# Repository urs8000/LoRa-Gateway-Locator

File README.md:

# LoRa-Gateway-Locator
This Node sends its position in selectable periods to all reachable gateways.
Analysing the received data on node API, where the gateway EUID is shown, 
a dotted map with the coverage of each gateway could be drawn.
made by https://github.com/gonzalocasas/ttn-coverage-tracker
**The data were also shown on JPMejier's http://ttnmapper.org/**

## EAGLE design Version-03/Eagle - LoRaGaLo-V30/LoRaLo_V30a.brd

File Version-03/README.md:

Based on Version 01/02
- Teensy 3.2
- GPS u-blox PAM-7Q with battary backup
- RFM95W (LoRa Radio 868MHz)
- OLED display (128x64) look careful when ordering. some have Vcc ans GND switched!
- navigation switches

this Version (03) added the following features
- debug/status LED (Common Anode RGB-LED, "Piranha diffused")
- PPS LED  (pulse per second)
- board mounted switches (wires could be connected for box mounted ones instead of them)
- second antenna connector (u.fl)
- GPS backup battery (CR1220)
- OpenLog SDcard based logger, connected via Serial3
  all sent positions will be logged, so it could be compared from where no connection to a given gateway could be established.

some explanations to the power supply:
getting the most out of 3 x 1.5V AA batteries and having stable 5V therefor I've added a xV to 5V step-up boost converter
The suggested Pololu step-up does not work correctly in contrary to the specification.
So I changed to another (bulkier) type found at eBay ( DC-DC Boost Converter Step Up 1-5V to 5V 500mA Module ) 
Because the layout is totally different, you have to solder it inbetween the batter case and the input pins and to bridge Vin-Vout.
If you plan to use a 5V power bank you just can bridge Vin and Vout and connect your supply instead of batteries to JPOWER

Tested on final boards, made by ITEAD Studio

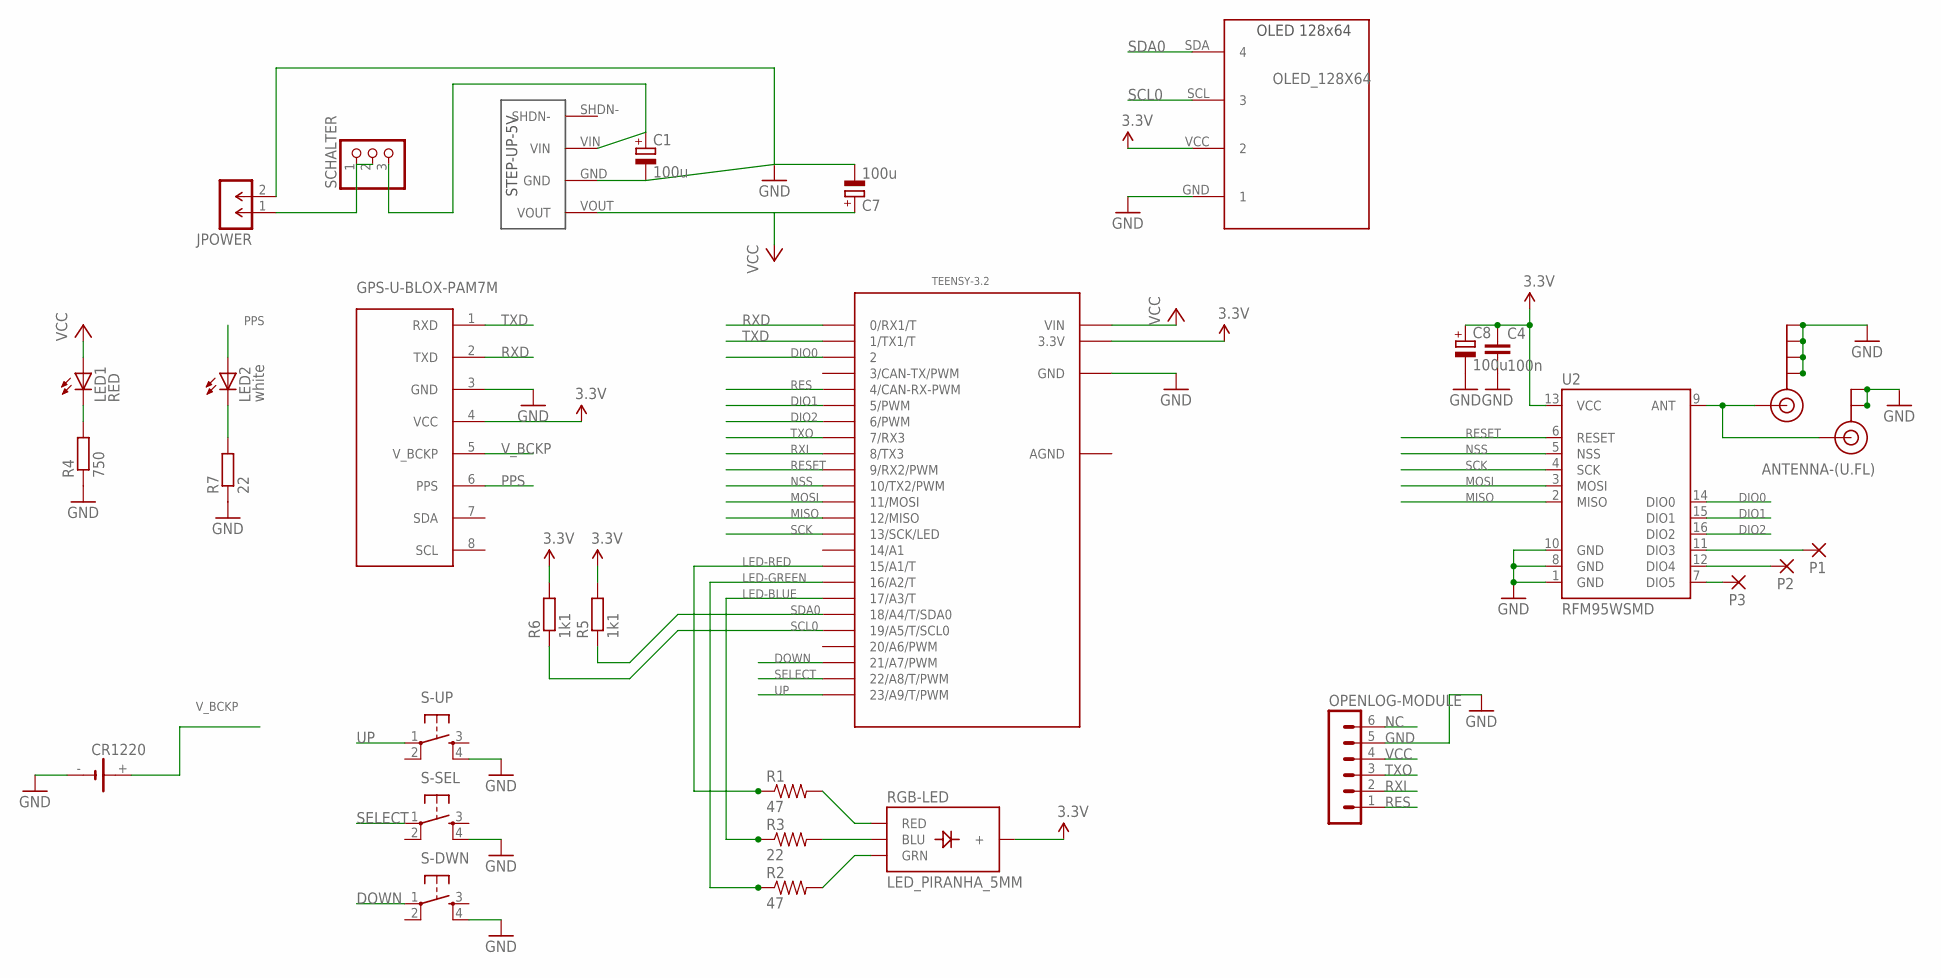
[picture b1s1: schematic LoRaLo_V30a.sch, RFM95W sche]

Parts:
ANTENNA-(EDGE-MOUNT): SMA_EDGE; SMA-EDGE
ANTENNA-(U.FL): U.FL
C1, C7, C8: 100u; PANASONIC_D
C4: 100n; C1206
CR1220: CH291-1220LF
GPS-U-BLOX-PAM7M: U-BLOX-PAM-7Q
JPOWER: M-1X02-SIP-100-40; SIP-100-02-40
LED1: RED; LED-1206
LED2: white; LED-1206
OLED_128X64: OLED_128X64
OPENLOG-MODULE: MA06-1
P1, P2, P3: 1,6/0,8
R1, R2: 47; 1206
R3: 22; 1206
R4: 750; M1206
R5, R6: 1k1; M1206
R7: 22; M1206
RGB-LED: LED_PIRANHA_5MM
S-DWN: TAC_SWITCHPTH; TACTILE-PTH
S-SEL: TAC_SWITCHPTH; TACTILE-PTH
S-UP: TAC_SWITCHPTH; TACTILE-PTH
SCHALTER: PINHD-1X3; 1X03
STEP-UP-5V: POLOLU_STEP-UP
TEENSY-3.2: TEENSY_3.1_DIL; TEENSY3-DIL
U2: RFM95WSMD; RFM95W_SMD

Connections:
3.3V: C4.1, C8.+, GPS-U-BLOX-PAM7M.4 (VCC), OLED_128X64.VCC (2), R5.2, R6.2, RGB-LED.+, TEENSY-3.2.3.3V, U2.13 (VCC)
AGND: TEENSY-3.2.AGND
DIO0: TEENSY-3.2.2, U2.14 (DIO0)
DIO1: TEENSY-3.2.5 (5/PWM), U2.15 (DIO1)
DIO2: TEENSY-3.2.6 (6/PWM), U2.16 (DIO2)
DOWN: S-DWN.1, TEENSY-3.2.21/A7 (21/A7/PWM)
GND: ANTENNA-(EDGE-MOUNT).GND@0 (GND), ANTENNA-(EDGE-MOUNT).GND@1 (GND), ANTENNA-(EDGE-MOUNT).GND@2 (GND), ANTENNA-(EDGE-MOUNT).GND@3 (GND), ANTENNA-(U.FL).P$1 (GND), ANTENNA-(U.FL).P$2 (GND), C1.-, C4.2, C7.-, C8.-, CR1220.-, GPS-U-BLOX-PAM7M.3 (GND), JPOWER.2, OLED_128X64.GND (1), OPENLOG-MODULE.5, R4.1, R7.1, S-DWN.4, S-SEL.4, S-UP.4, STEP-UP-5V.GND, TEENSY-3.2.GND, U2.1 (GND), U2.8 (GND), U2.10 (GND)
LED-BLUE: R3.1, TEENSY-3.2.17/A3 (17/A3/T)
LED-GREEN: R2.1, TEENSY-3.2.16/A2 (16/A2/T)
LED-RED: R1.1, TEENSY-3.2.15/A1 (15/A1/T)
MISO: TEENSY-3.2.12 (12/MISO), U2.2 (MISO)
MOSI: TEENSY-3.2.11 (11/MOSI), U2.3 (MOSI)
unnamed: R1.2, RGB-LED.R (RED)
unnamed: P1.1, U2.11 (DIO3)
unnamed: R2.2, RGB-LED.G (GRN)
unnamed: C1.+, SCHALTER.3, STEP-UP-5V.VIN
unnamed: ANTENNA-(EDGE-MOUNT).SIG (SIGNAL), ANTENNA-(U.FL).P$3 (SIGNAL), U2.9 (ANT)
unnamed: P2.1, U2.12 (DIO4)
unnamed: P3.1, U2.7 (DIO5)
unnamed: R3.2, RGB-LED.B (BLU)
unnamed: JPOWER.1, SCHALTER.1, SCHALTER.2
unnamed: LED2.C, R7.2
unnamed: LED1.C, R4.2
NC: OPENLOG-MODULE.6
NSS: TEENSY-3.2.10 (10/TX2/PWM), U2.5 (NSS)
PPS: GPS-U-BLOX-PAM7M.6 (PPS), LED2.A
RES: OPENLOG-MODULE.1, TEENSY-3.2.4 (4/CAN-RX-PWM)
RESET: TEENSY-3.2.9 (9/RX2/PWM), U2.6 (RESET)
RXD: GPS-U-BLOX-PAM7M.2 (TXD), TEENSY-3.2.0 (0/RX1/T)
RXI: OPENLOG-MODULE.2, TEENSY-3.2.8 (8/TX3)
SCK: TEENSY-3.2.13 (13/SCK/LED), U2.4 (SCK)
SCL0: OLED_128X64.SCL (3), R6.1, TEENSY-3.2.19/A5 (19/A5/T/SCL0)
SDA0: OLED_128X64.SDA (4), R5.1, TEENSY-3.2.18/A4 (18/A4/T/SDA0)
SELECT: S-SEL.1, TEENSY-3.2.22/A8 (22/A8/T/PWM)
TXD: GPS-U-BLOX-PAM7M.1 (RXD), TEENSY-3.2.1 (1/TX1/T)
TXO: OPENLOG-MODULE.3, TEENSY-3.2.7 (7/RX3)
UP: S-UP.1, TEENSY-3.2.23/A9 (23/A9/T/PWM)
VCC: C7.+, LED1.A, OPENLOG-MODULE.4, STEP-UP-5V.VOUT, TEENSY-3.2.VIN
V_BCKP: CR1220.+, GPS-U-BLOX-PAM7M.5 (V_BCKP)

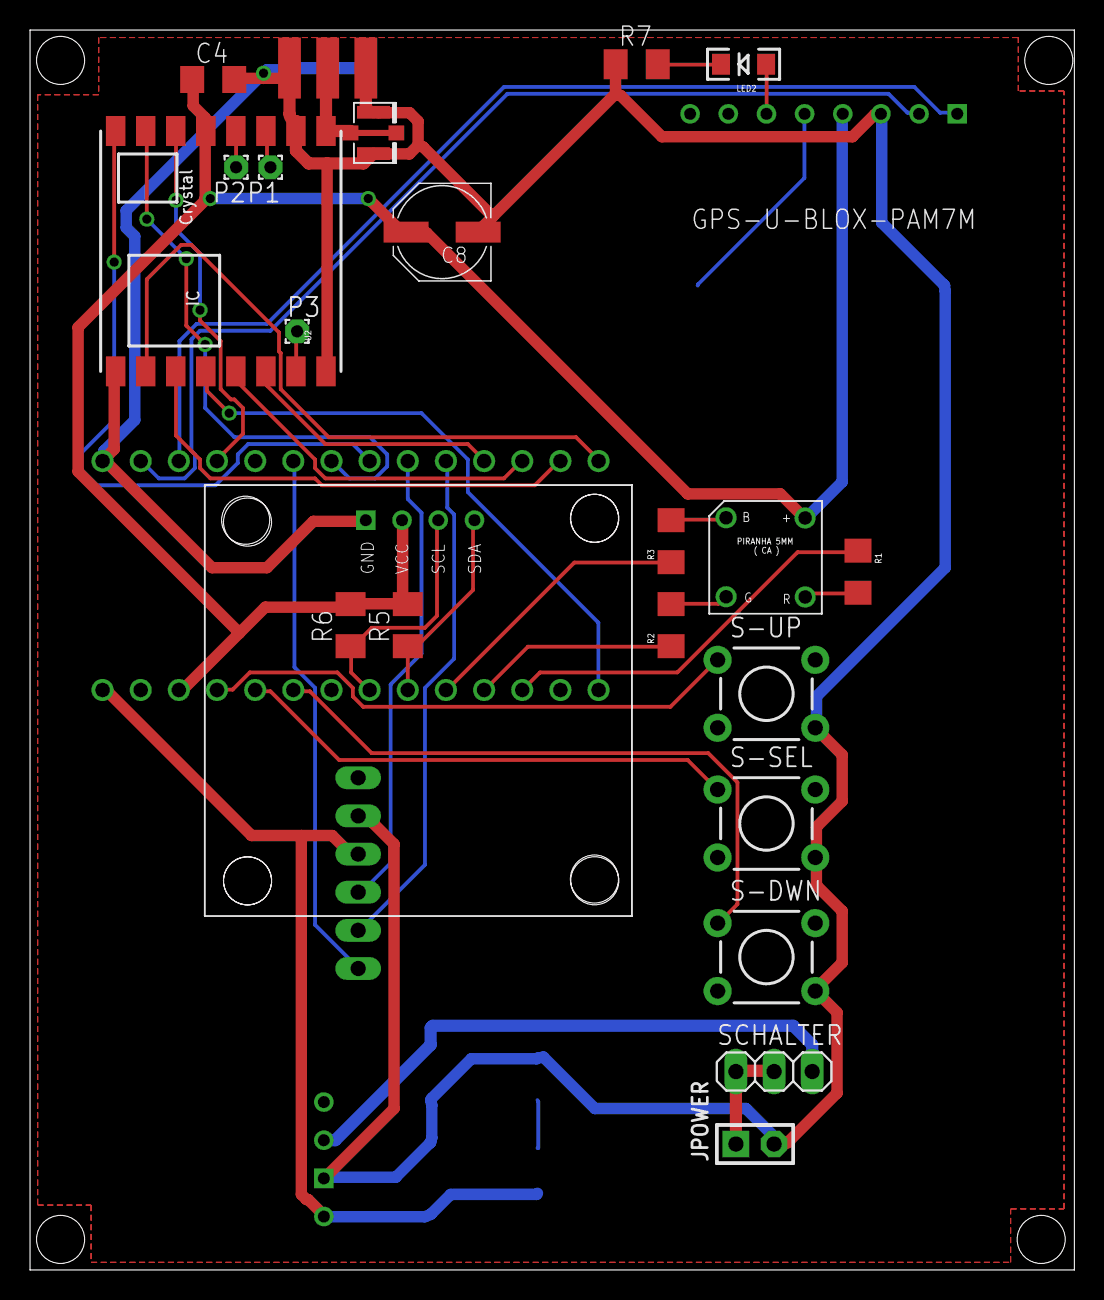
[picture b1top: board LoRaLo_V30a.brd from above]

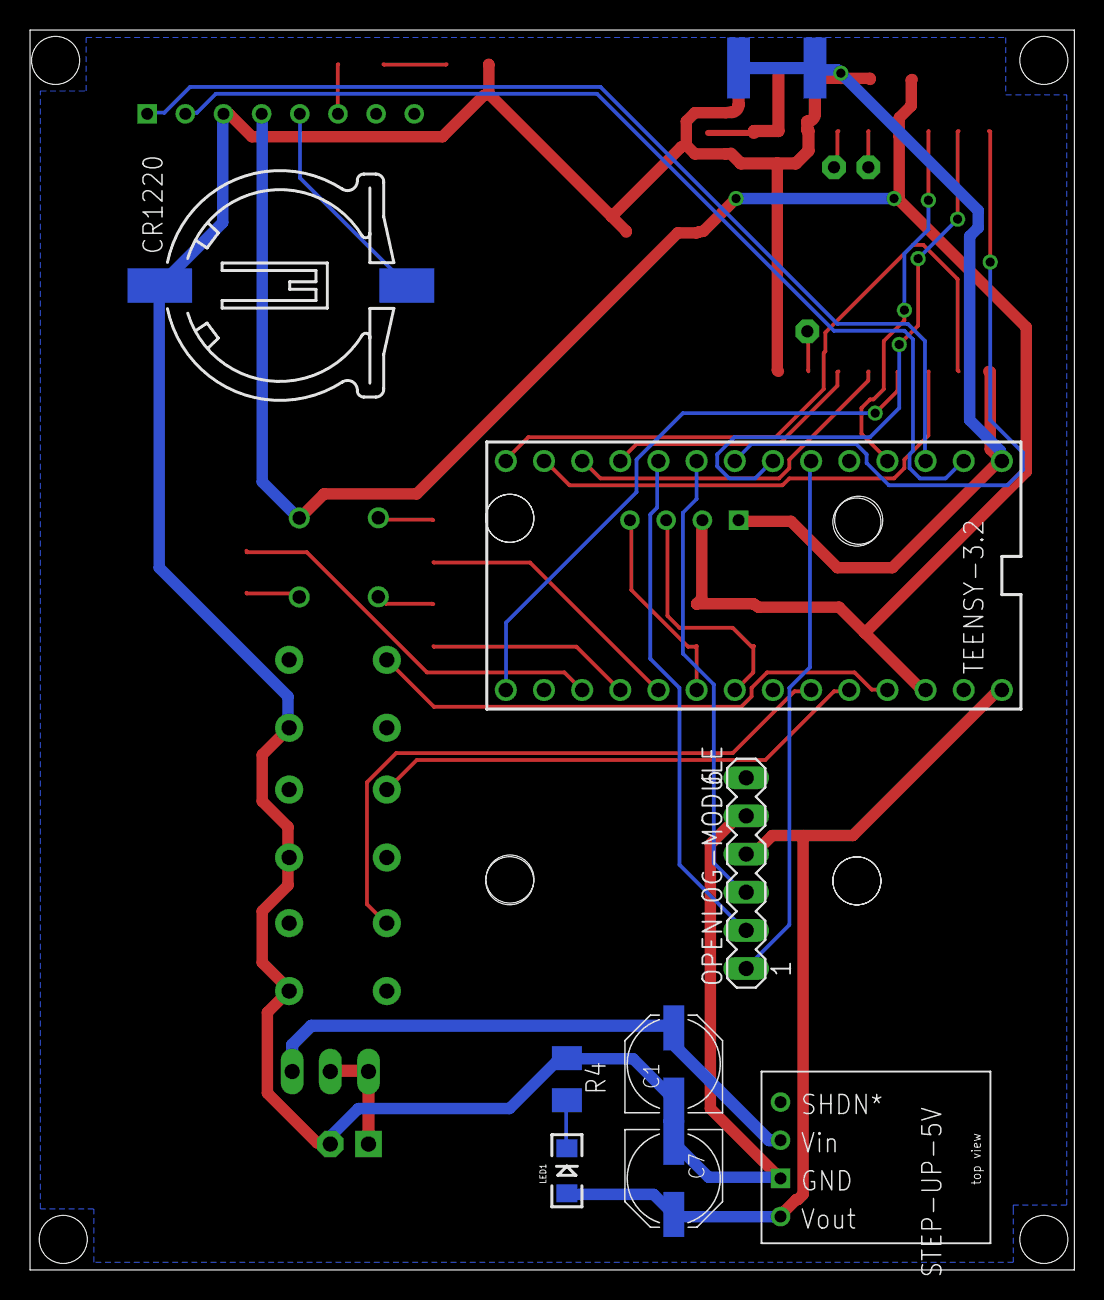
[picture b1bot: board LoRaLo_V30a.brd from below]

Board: 2 copper layers, 69.5 x 82.5 mm, 31 parts (8 on the bottom side), 37 nets.

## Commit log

2016-01-28 Create Version-01
2016-01-29 Version 01 with schema, board layout und the needed corrections
    this version needs two wires to run fully funcional
2016-02-01 added some fotos
2016-02-01 enhanced Version 02
    see readme
2016-02-02 programes for V1 & V2 added
2016-02-14 immediate run fixed
    now selecting a timed transmittion, it runs at the first time
    immediately
2016-02-14 final Version 2.0 (pre ordering)
    the Eagle files base on a breadboard implementation
    np dual layer board tested until now (14.02.2016)
2016-02-14 tag added to the board
2016-02-14 some important notes in README added
    power supply
2016-02-15 one trace fixed
2016-02-16 V20-2 Rerouted
    a better routed board
    also 4 holes for the OLED
2016-02-19 node address hidden
    change that address to your own one
2016-02-19 channel fix
2016-04-06 V20 deleted
2016-04-06 V01 & V02 deleted, Version-03 added
2016-04-06 V10 & V20 deleted, V30 added
2016-06-12 map info updated

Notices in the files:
parts and their libraries:
SparkFun-Connectors: Licensing: Creative Commons ShareAlike 4.0 International - https://creativecommons.org/licenses/by-sa/4.0
con-headers-jp: Copyright (C) 2008, Bob Starr
SparkFun-LED: Licensing: CC v3.0 Share-Alike You are welcome to use this library for commercial purposes.
